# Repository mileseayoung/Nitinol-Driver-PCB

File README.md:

# Nitinol-Driver-PCB
The latest files related to the development of a low-cost, hobbyist-friendly nitinol wire driver PCB, with a PWM input and self-sensed position output.

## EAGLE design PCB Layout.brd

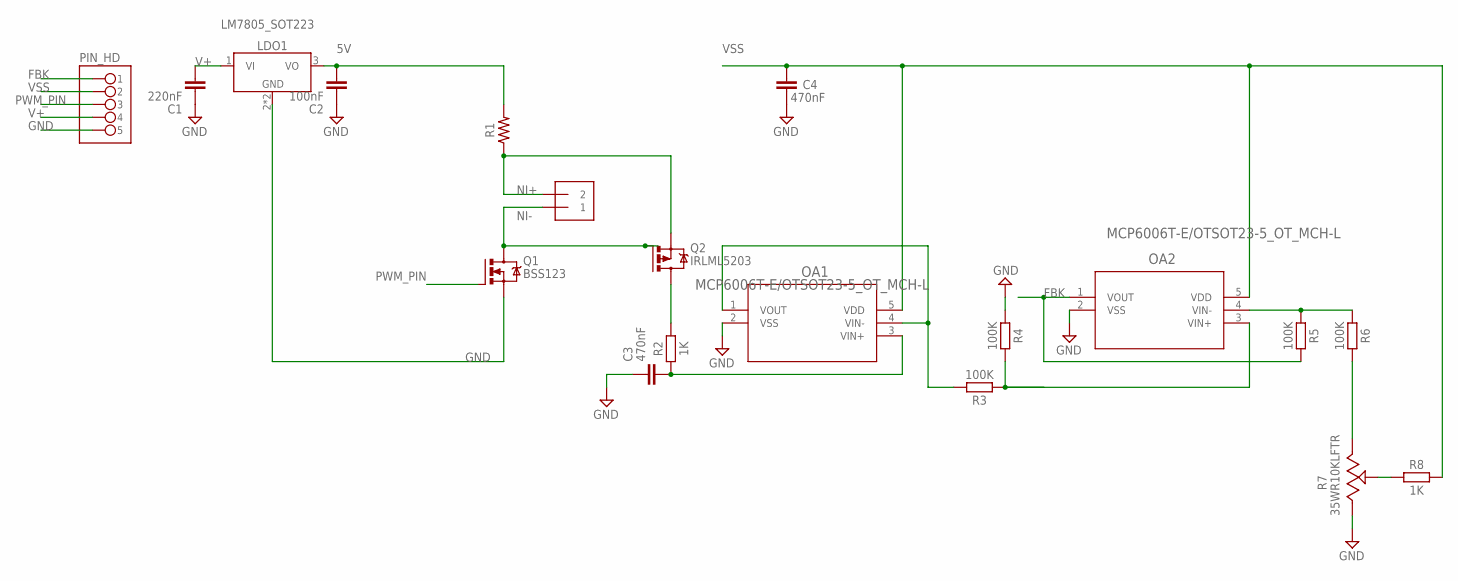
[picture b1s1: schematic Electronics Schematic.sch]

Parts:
C1: 220nF; CAPC1005X60
C2: 100nF; CAPC1005X60
C3, C4: 470nF; CAPC1005X60
LDO1: LM7805_SOT223; SOT230P700X170-4
NITI: 1X2-3.5MM
OA1, OA2: MCP6006T-E/OTSOT23-5_OT_MCH-L; SOT23-5_OT_MCH-L
PIN_HD: PINHD-1X05_1X05M; 1X05
Q1: BSS123; SOT23
Q2: IRLML5203; SOT23
R1: R-US_AXIAL-11.7MM-PITCH; RESAD1176W63L850D250B
R2, R8: 1K; RESC1005X40
R3, R4, R5, R6: 100K; RESC1005X40
R7: 35WR10KLFTR; TRIM_35WR10KLFTR

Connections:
5V: C2.2, LDO1.3 (VO), R1.2
FBK: OA2.1 (VOUT), PIN_HD.1, R5.2
GND: C1.1, C2.1, C3.1, C4.1, LDO1.2 (GND), LDO1.4 (GND), OA1.2 (VSS), OA2.2 (VSS), PIN_HD.5, Q1.2 (S), R4.1, R7.1
unnamed: Q2.3 (D), R2.2
unnamed: R7.2, R8.1
unnamed: OA2.4 (VIN-), R5.1, R6.1
unnamed: OA2.3 (VIN+), R3.1, R4.2
unnamed: R6.2, R7.3
unnamed: OA1.1 (VOUT), OA1.4 (VIN-), R3.2
NI+: NITI.2, Q2.2 (S), R1.1
NI-: NITI.1, Q1.3 (D), Q2.1 (G)
PWM_PIN: PIN_HD.3, Q1.1 (G)
R2_TEST: C3.2, OA1.3 (VIN+), R2.1
V+: C1.2, LDO1.1 (VI), PIN_HD.4
VSS: C4.2, OA1.5 (VDD), OA2.5 (VDD), PIN_HD.2, R8.2

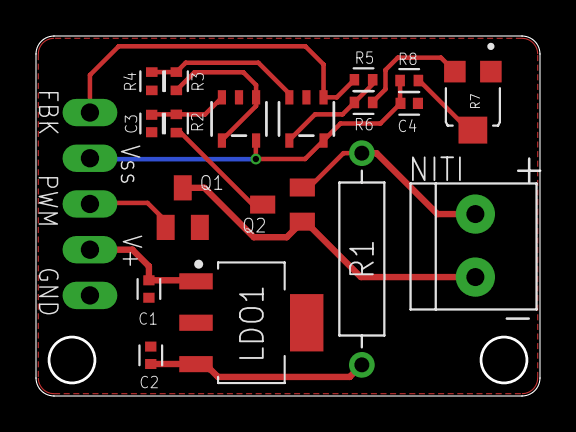
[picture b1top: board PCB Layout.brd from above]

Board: 2 copper layers, 27.8 x 19.8 mm, 19 parts (1 on the bottom side), 15 nets.

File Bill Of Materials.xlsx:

| Callout | Model # | Manufacturer | Value | Description | Price ($) |  | Password to unprotect sheet: password
 | LDO1 | LM7805MP/NOPB | Texas Instruments | - | IC REG LINEAR 5V 1.5A SOT223-4 | 1.3
 | Q1 | BSS306NH6327XTSA1 | Infineon Technologies | - | MOSFET N-CH 30V 2.3A SOT23-3 | 0.23100000000000001
 | Q2 | IRLML6401TRPBF | Infineon Technologies | - | MOSFET P-CH 12V 4.3A SOT23 | 0.26800000000000002
 | OA1 | MCP6006T-E/OT | Microchip Technology | - | IC OPAMP GP 1 CIRCUIT SOT23-5 | 0.17
 | OA2 | MCP6006T-E/OT | Microchip Technology | - | IC OPAMP GP 1 CIRCUIT SOT23-5 | 0.17
 | C1 | CL05B224KO5NNNC | Samsung Electro-Mechanics | 220 nF | CAP CER 0.22UF 16V X7R 0402 | 1.78E-2
 | C2 | CL05B104KP5NNNC | Samsung Electro-Mechanics | 100 nF | CAP CER 0.1UF 10V X7R 0402 | 8.8000000000000005E-3
 | C3 | CL05A474KP5NNNC | Samsung Electro-Mechanics | 470 nF | CAP CER 0.47UF 10V X5R 0402 | 2.86E-2
 | C4 | CL05A474KP5NNNC | Samsung Electro-Mechanics | 470 nF | CAP CER 0.47UF 10V X5R 0402 | 2.86E-2
 | NITINOL | - | Dynalloy | - | Flexinol Wire 0.006" HT, 20cm | 1.1299999999999999
 | R1 | RSMF2JT1R00 | Stackpole Electronics, Inc. | 1 Ohm | RES 1 OHM 5% 2W AXIAL | 0.17760000000000001
 | R2 | ERJ-2RKF1001X | Panasonic Electronic Components | 1 kOhm | RES SMD 1K OHM 1% 1/10W 0402 | 1.52E-2
 | R3 | ERJ-2RKF1003X | Panasonic Electronic Components | 100 kOhm | RES SMD 100K OHM 1% 1/10W 0402 | 1.52E-2
 | R4 | ERJ-2RKF1803X | Panasonic Electronic Components | 180 kOhm | RES SMD 180K OHM 1% 1/10W 0402 | 1.52E-2
 | R5 | ERJ-2RKF1803X | Panasonic Electronic Components | 180 kOhm | RES SMD 180K OHM 1% 1/10W 0402 | 1.52E-2
 | R6 | ERJ-2RKF1003X | Panasonic Electronic Components | 100 kOhm | RES SMD 100K OHM 1% 1/10W 0402 | 1.52E-2
 | R7 | 35WR10KLFTR | TT Electronics/BI | 10 kOhm | TRIMMER 10K OHM 0.1W SMD TOP | 0.55800000000000005
 | R8 | ERJ-2RKF1001X | Panasonic Electronic Components | 1 kOhm | RES SMD 1K OHM 1% 1/10W 0402 | 1.52E-2
 | TB1 | 1984617 | Phoenix Contact | - | TERM BLK 2POS SIDE ENT 3.5MM | 0.59799999999999998
 | PCB | - | OSHPark | - | 2-Layer Custom PCB, 0.877in^2 | 1.45
 |  |  |  |  | Total Cost: | 6.2276000000000007

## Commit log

2025-01-29 v2.3 File Upload

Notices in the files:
parts and their libraries:
MCP6006T_E_OT: COPYRIGHT: Copyright (C) 2024 Ultra Librarian. All rights reserved.
